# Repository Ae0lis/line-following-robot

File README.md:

# Autonomous Line-Following Robot

A custom-PCB line-following robot built for the EE 201 capstone at the University
of Washington. This was a one-month competition to design the fastest,
most accurate line follower in the class.

**Full writeup:** https://ae0lis.github.io/projects/line_robot/

## Overview

The robot follows a black line on a light surface using a custom seven-channel
photoresistor array, processes the readings through a PID controller on an Arduino,
and steers by driving its two motors at differing speeds. Built by a three-person
team over one month; completed the full competition track.

## Repository structure

| Path | Contents |
|------|----------|
| `kicad/` | KiCad project — schematic, board layout, and netlist for the sensor array |
| `kicad/PCB_share/` | Gerber + drill files for fabrication (open in any Gerber viewer, no KiCad needed) |
| `firmware/` | Arduino control code (see note below) |
| `renders/` | Exported schematic and 3D board renders |
| `images/` | Photos of the assembled robot |
| `diagrams/` | Diagrams for explaining the robot's systems |

## The sensor board

The core of the project is a custom PCB I designed and laid out in KiCad:

- **Seven-channel photoresistor array** — each channel pairs a photoresistor with an
  LED, flooding the surface with consistent light so a change in reading reflects
  floor color rather than ambient light or shadow.
- **Per-LED current limiting** — each LED has its own 1 kΩ resistor.
- **Copper pours** for GND and VCC instead of hand-routed power traces, which helped
  keep the board compact (40 × 80 mm between mounting holes).
- **Sensor outputs map to Arduino analog pins A8–A14**, matching the firmware.

## Firmware

The control firmware is based on PID scaffolding provided to all teams in the course.
My contribution here was mapping the controller to this board's pin assignments,
configuring it, and tuning the PID constants against the competition track. Both
files are included for transparency:

- `10_5_line_follower_code_template.ino` — the course-provided starting point
- `10_5_line_follower_code_completed.ino` — the filled-in, tuned version used in the robot

Tuned constants at competition: S 30, P 24, I 0, D 24.
Calibrated sensor readings: ~2500 on black, ~1000 on white.

## Viewing the board

- **Renders:** the PNGs in `renders/` show the schematic and 3D board.
- **Gerbers:** open `kicad/PCB_share/` in any Gerber viewer to inspect the manufacturing layers.
- **Source:** open `kicad/Final_Project_PCB.kicad_pro` in KiCad 9.0 or newer. 
			  May work on older versions, but no promises!

## Team

Built by Dat Ly, Michael Zhang, and Ben Robison for EE 201 (University of Washington).
I (Ben) was responsible for the sensor PCB, firmware configuration and tuning, and much of
the physical assembly.

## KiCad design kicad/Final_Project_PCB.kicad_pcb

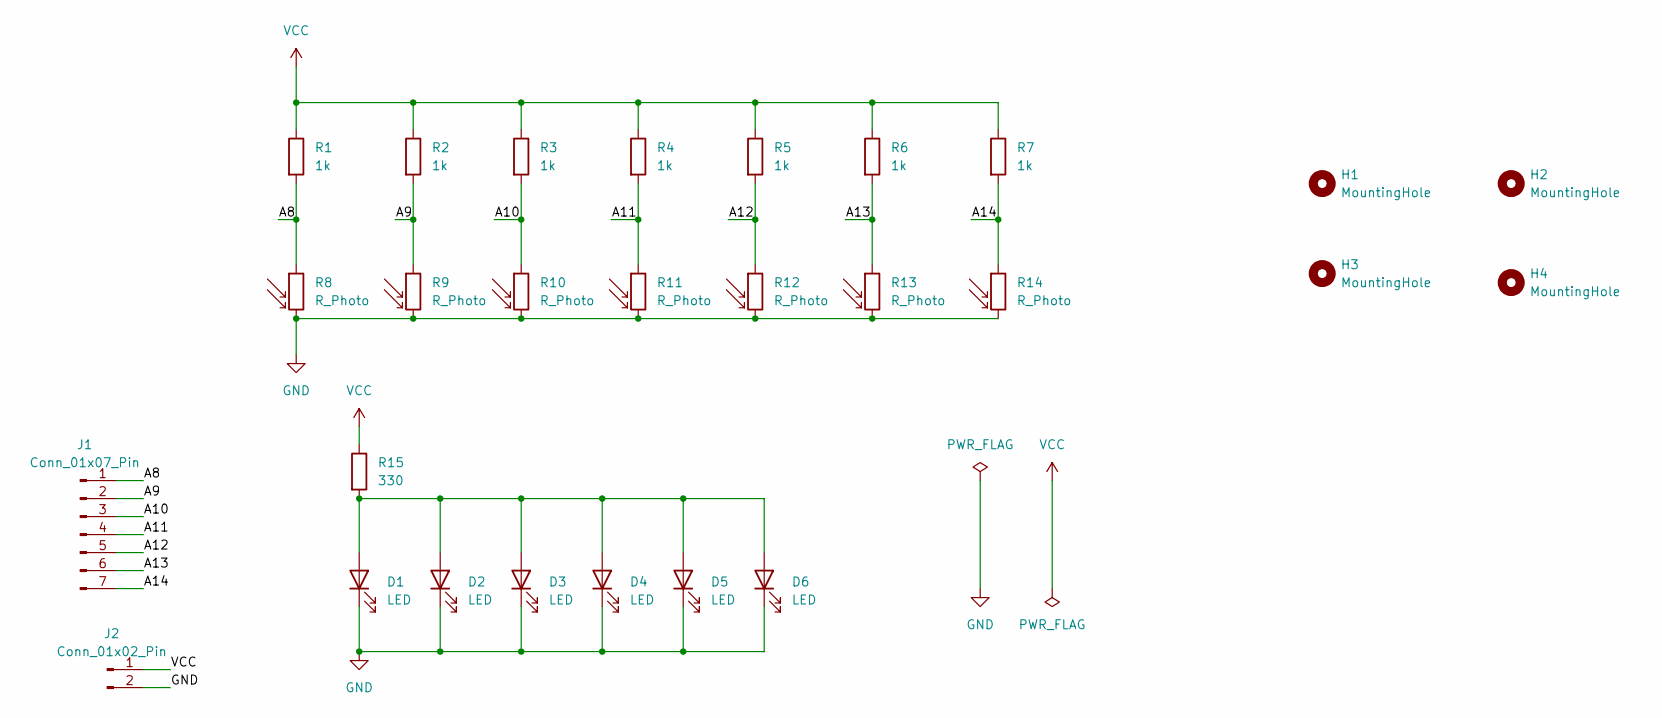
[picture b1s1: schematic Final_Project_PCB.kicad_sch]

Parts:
D1, D2, D3, D4, D5, D6: LED; LED_D5.0mm
H1, H2, H3, H4: MountingHole; MountingHole_3.2mm_M3
J1: Conn_01x07_Pin; PinHeader_1x07_P2.54mm_Vertical
J2: Conn_01x02_Pin; PinHeader_1x02_P2.54mm_Vertical
R1, R2, R3, R4, R5, R6, R7: 1k; R_Axial_DIN0207_L6.3mm_D2.5mm_P10.16mm_Horizontal
R8, R9, R10, R11, R12, R13, R14: R_Photo; R_LDR_5.0x4.1mm_P3mm_Vertical
R15: 330; R_Axial_DIN0207_L6.3mm_D2.5mm_P10.16mm_Horizontal

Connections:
/A8: J1.1, R1.2, R8.1
/A9: J1.2, R2.2, R9.1
/A10: J1.3, R3.2, R10.1
/A11: J1.4, R4.2, R11.1
/A12: J1.5, R5.2, R12.1
/A13: J1.6, R6.2, R13.1
/A14: J1.7, R7.2, R14.1
GND: D1.1 (K), D2.1 (K), D3.1 (K), D4.1 (K), D5.1 (K), D6.1 (K), J2.2, R8.2, R9.2, R10.2, R11.2, R12.2, R13.2, R14.2
unnamed: D1.2 (A), D2.2 (A), D3.2 (A), D4.2 (A), D5.2 (A), D6.2 (A), R15.2
VCC: J2.1, R1.1, R2.1, R3.1, R4.1, R5.1, R6.1, R7.1, R15.1

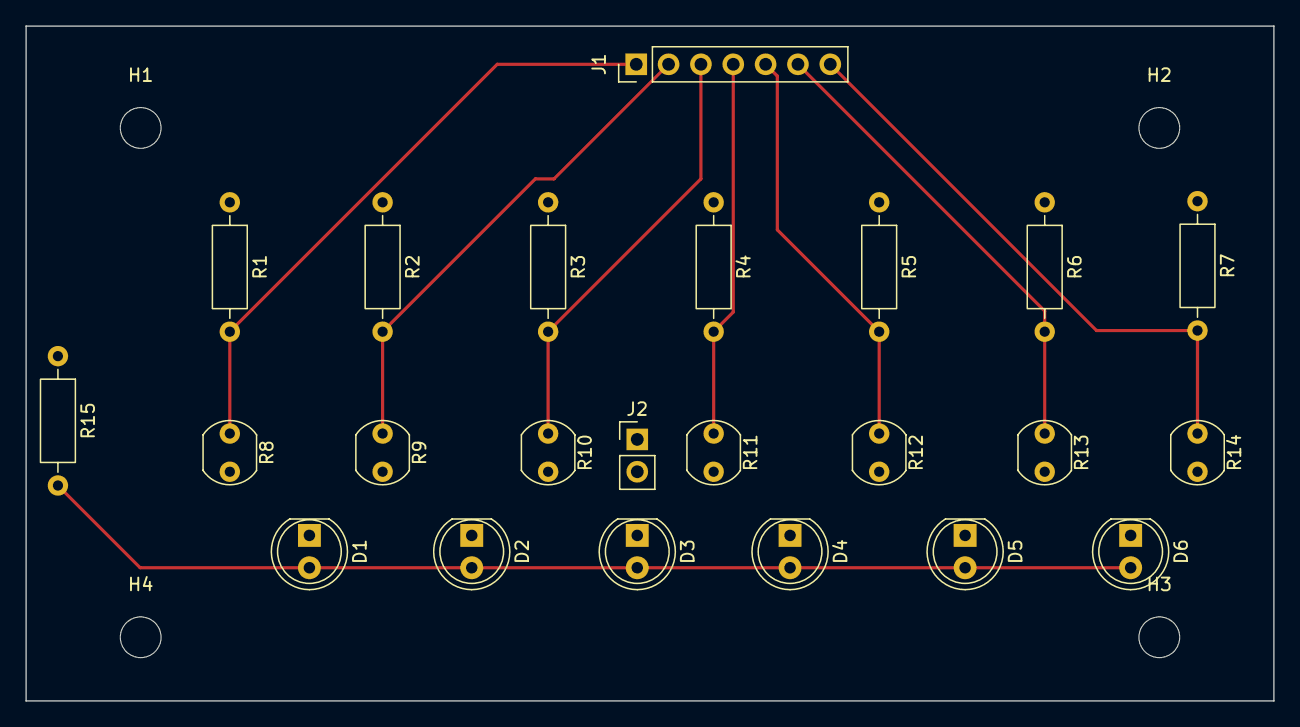
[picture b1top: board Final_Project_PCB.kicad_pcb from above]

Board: 2 copper layers, 98.0 x 53.0 mm, 27 parts (0 on the bottom side), 10 nets.

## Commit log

2026-06-12 Add KiCad sensor board, firmware, and renders
2026-06-12 Add README and photos
2026-06-12 Update competition description in README
    Clarified the description of the competition.
2026-06-12 Added block diagram
2026-06-12 Image display fix
2026-06-12 Diagram position change
